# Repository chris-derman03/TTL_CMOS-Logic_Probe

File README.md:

This project was developed in KiCad 10.0

The original circuit design was adapted from the below article.

Axelson, J. (1990). "Experimenter's Logic Probe."
*Electronic Experimenter's Handbook*, Popular Electronics.

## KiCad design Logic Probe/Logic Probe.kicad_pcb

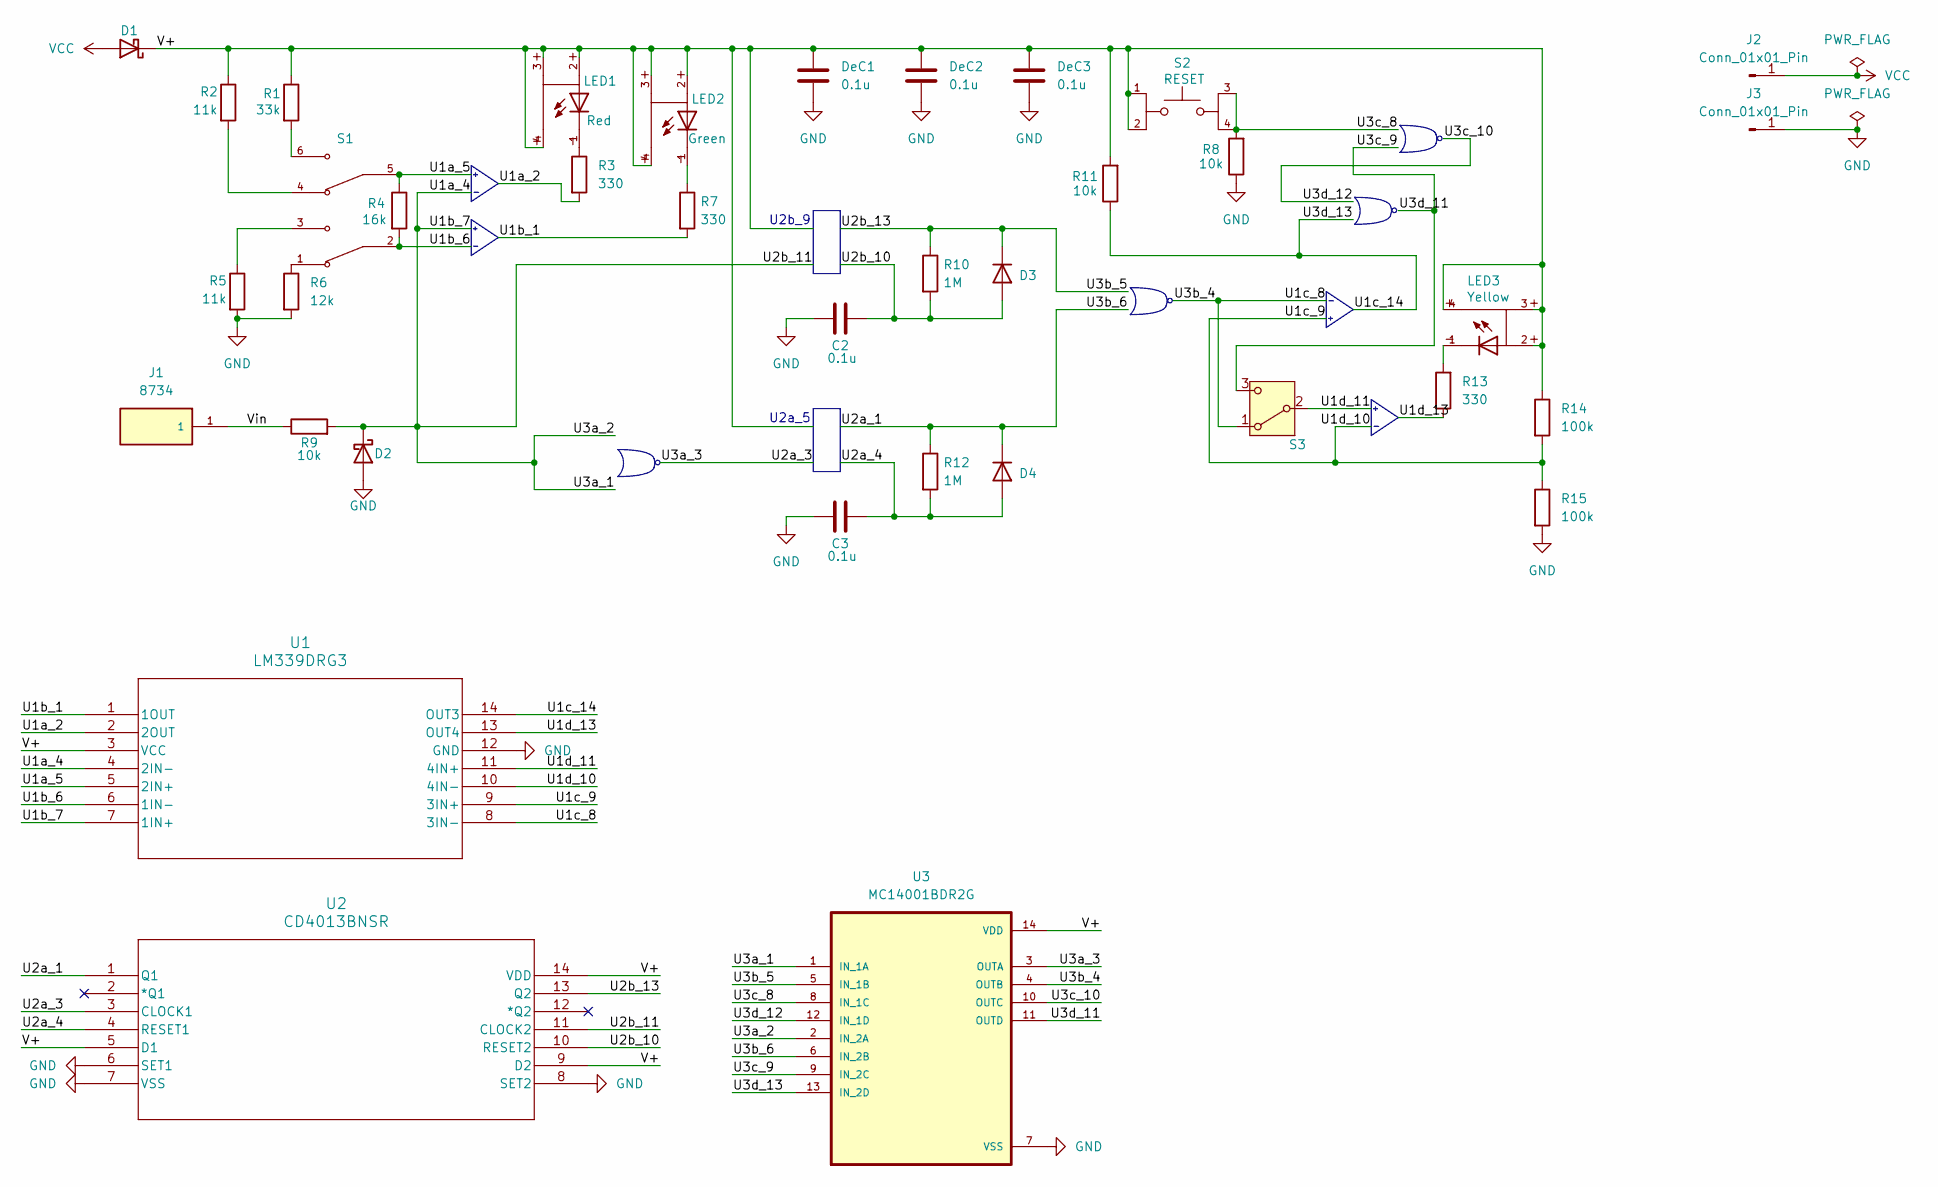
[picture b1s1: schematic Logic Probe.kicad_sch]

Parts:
C2, C3: 0.1u; C_0805_2012Metric_Pad1.18x1.45mm_HandSolder
D1, D2: D_Schottky; D_DO-35_SOD27_P7.62mm_Horizontal
D3, D4: D; DIOAD753W49L380D172B
DeC1, DeC2, DeC3: 0.1u; C_0805_2012Metric_Pad1.18x1.45mm_HandSolder
J1: 8734; KEYSTONE_8734; PARTREV 7.13.16; DigiKey_Part_Number 36-8734-ND
J2, J3: Conn_01x01_Pin; PinHeader_1x01_P2.54mm_Vertical
LED1: Red; WL-SMTW_3528_PLCC4
LED2: Green; WL-SMTW_3528_PLCC4
LED3: Yellow; WL-SMTW_3528_PLCC4
R1: 33k; RESC2012X65N
R2, R5: 11k; RESC2012X65N
R3, R7, R13: 330; RES_R1220_ROM-M
R4: 16k; RESC2012X65N
R6: 12k; RESC2012X65N
R8, R9, R11: 10k; RESC2012X65N
R10, R12: 1M; R_0805_2012Metric_Pad1.20x1.40mm_HandSolder
R14, R15: 100k; R_0805_2012Metric_Pad1.20x1.40mm_HandSolder
S1: SLW-135987-5A-N-D; SW_SLW-135987-5A-N-D; PARTREV 1.01
S2: RESET; SW_TL1105BF160Q; PARTREV A
S3: SW_SPDT; SW_SLW-12689-4A-N-D
U1: LM339DRG3; D14-M
U2: CD4013BNSR; NS14-M
U3: MC14001BDR2G; SOIC127P600X175-14N

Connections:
/U1a_2: R3.2, U1.2 (2OUT)
/U1a_4: D2.1 (K), R9.2, U1.4 (2IN-), U1.7 (1IN+), U2.11 (CLOCK2), U3.1 (IN_1A), U3.2 (IN_2A)
/U1a_5: R4.1, S1.5, U1.5 (2IN+)
/U1b_1: R7.2, U1.1 (1OUT)
/U1b_6: R4.2, S1.2, U1.6 (1IN-)
/U1c_8: S3.1 (A), U1.8 (3IN-), U3.4 (OUTB)
/U1c_9: R14.2, R15.1, U1.9 (3IN+), U1.10 (4IN-)
/U1c_14: R11.1, U1.14 (OUT3), U3.13 (IN_2D)
/U1d_11: S3.2 (B), U1.11 (4IN+)
/U1d_13: R13.1, U1.13 (OUT4)
/U2a_1: D4.K, R12.1, U2.1 (Q1), U3.6 (IN_2B)
/U2a_3: U2.3 (CLOCK1), U3.3 (OUTA)
/U2a_4: C3.2, D4.A, R12.2, U2.4 (RESET1)
/U2b_10: C2.2, D3.A, R10.2, U2.10 (RESET2)
/U2b_13: D3.K, R10.1, U2.13 (Q2), U3.5 (IN_1B)
/U3c_8: R8.2, S2.3, S2.4, U3.8 (IN_1C)
/U3c_9: S3.3 (C), U3.9 (IN_2C), U3.11 (OUTD)
/U3c_10: U3.10 (OUTC), U3.12 (IN_1D)
/V+: D1.1 (K), DeC1.1, DeC2.1, DeC3.1, LED1.2, LED1.3, LED1.4, LED2.2, LED2.3, LED2.4, LED3.2, LED3.3, LED3.4, R1.1, R2.1, R11.2, R14.1, S2.1, S2.2, U1.3 (VCC), U2.5 (D1), U2.9 (D2), U2.14 (VDD), U3.14 (VDD); also elsewhere on the board
/Vin: J1.1 (1_1), R9.1
GND: C2.1, C3.1, D2.2 (A), DeC1.2, DeC2.2, DeC3.2, J3.1 (Pin_1_1), R5.2, R6.2, R8.1, R15.2, U1.12 (GND), U2.6 (SET1), U2.7 (VSS), U2.8 (SET2), U3.7 (VSS); also elsewhere on the board
unnamed: LED1.1, R3.1
unnamed: LED2.1, R7.1
unnamed: LED3.1, R13.2
unnamed: R1.2, S1.6
unnamed: R2.2, S1.4
unnamed: R5.1, S1.3
unnamed: R6.1, S1.1
VCC: D1.2 (A), J2.1 (Pin_1_1)

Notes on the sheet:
U2a_5
U2b_9

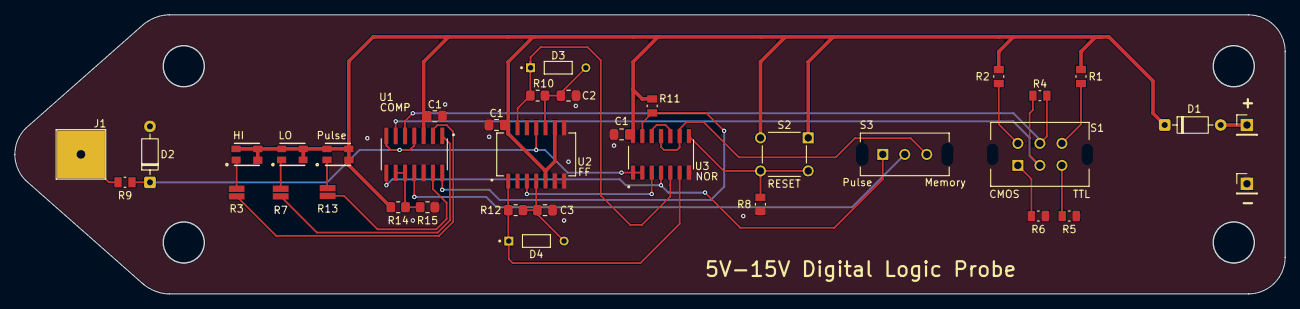
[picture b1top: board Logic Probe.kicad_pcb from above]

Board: 2 copper layers, 173.0 x 38.0 mm, 36 parts (0 on the bottom side), 29 nets.

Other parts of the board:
C1, C1#2, C1#3: 0.1u; C_0805_2012Metric_Pad1.18x1.45mm_HandSolder

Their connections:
/V+: C1.1, C1#2.1, C1#3.1; also elsewhere on the board
GND: C1.2, C1#2.2, C1#3.2; also elsewhere on the board
